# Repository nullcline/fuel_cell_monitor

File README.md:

# fuel_cell_monitor
[school] a sponsored capstone project to design a low-cost, scalable, voltage monitoring system that was capable of measuring a wide voltage range

here are some cool pics (i designed, manufactured, and tested the module).

you can read about the design in the included report [here](https://github.com/nullcline/fuel_cell_monitor/blob/main/design_report.pdf)

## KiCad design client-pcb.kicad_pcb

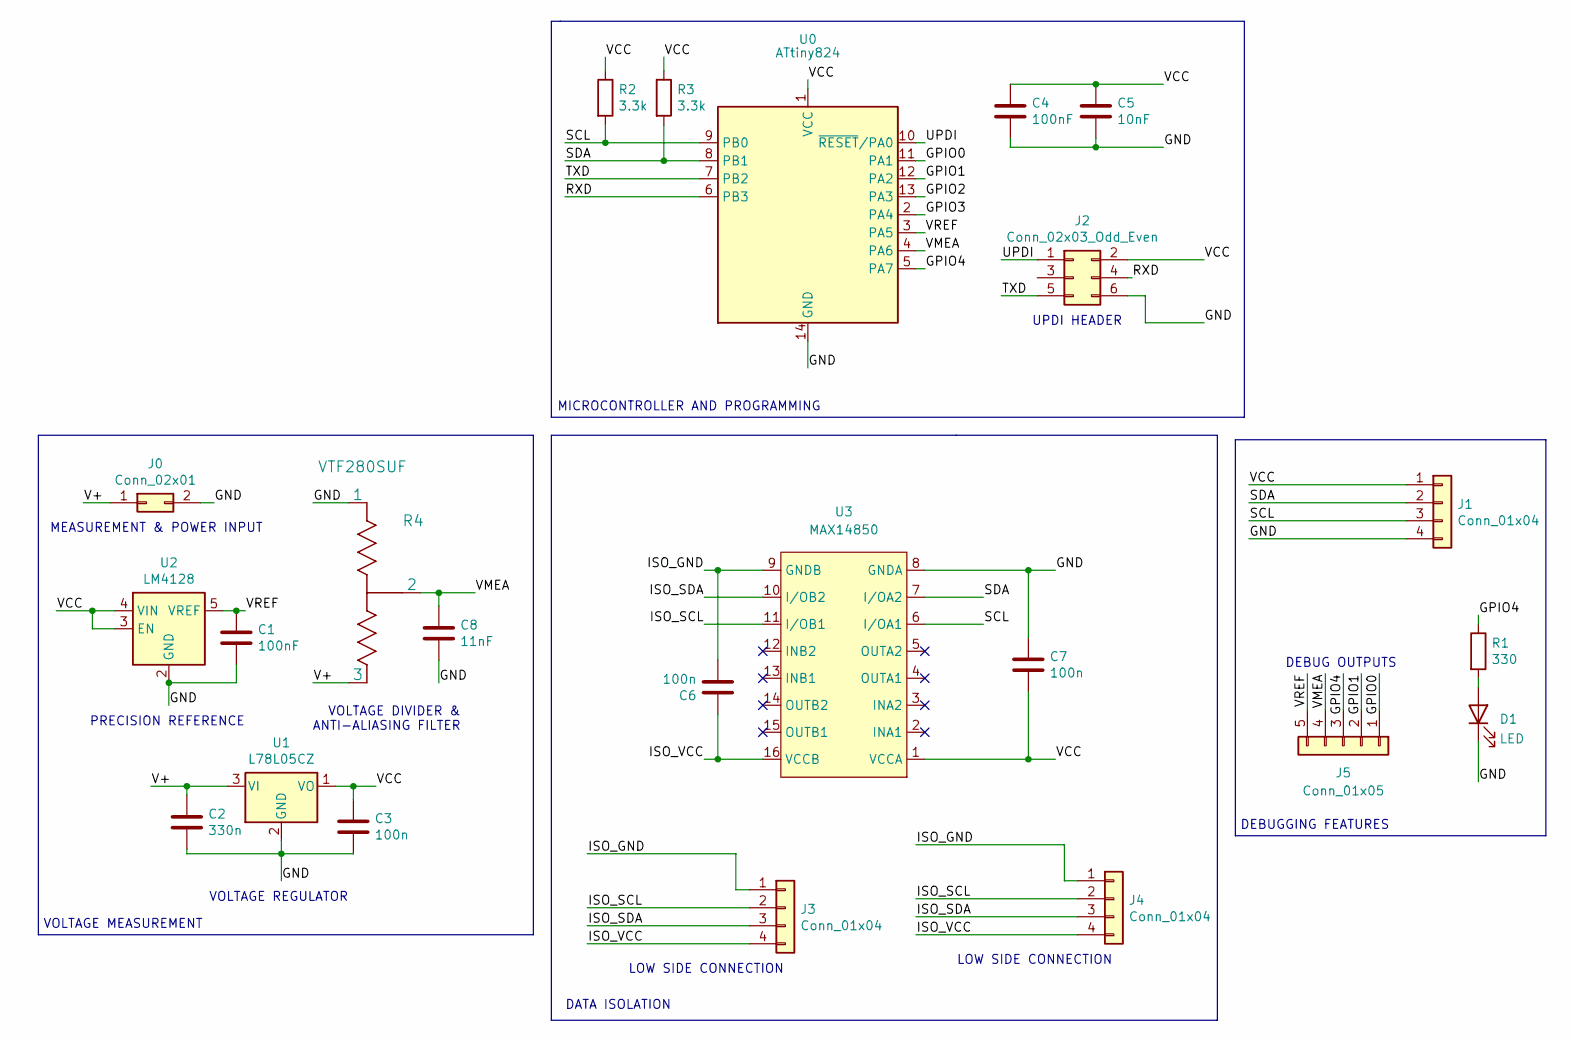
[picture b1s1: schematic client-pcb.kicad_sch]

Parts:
C1, C4: 100nF; C_1210_3225Metric_Pad1.33x2.70mm_HandSolder
C2: 330n; C_1210_3225Metric_Pad1.33x2.70mm_HandSolder
C3, C6, C7: 100n; C_1210_3225Metric_Pad1.33x2.70mm_HandSolder
C5: 10nF; C_1210_3225Metric_Pad1.33x2.70mm_HandSolder
C8: 11nF; C_1210_3225Metric_Pad1.33x2.70mm_HandSolder
D1: LED; LED_1210_3225Metric_Pad1.42x2.65mm_HandSolder
J0: Conn_02x01; TerminalBlock_Altech_AK300-2_P5.00mm
J1, J3, J4: Conn_01x04; PinHeader_1x04_P2.54mm_Vertical
J2: Conn_02x03_Odd_Even; PinHeader_2x03_P2.54mm_Vertical
J5: Conn_01x05; PinHeader_1x05_P2.54mm_Vertical
R1: 330; R_1210_3225Metric_Pad1.30x2.65mm_HandSolder
R2, R3: 3.3k; R_1210_3225Metric_Pad1.30x2.65mm_HandSolder
R4: VTF280SUF; PinSocket_1x03_P2.54mm_Vertical
U0: ATtiny824; SOIC-14_3.9x8.7mm_P1.27mm
U1: L78L05CZ; TO-92_Inline
U2: LM4128; SOT-23-5
U3: MAX14850; SOP-16_3.9x9.9mm_P1.27mm

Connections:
/GND: C1.2, C2.2, C3.2, C4.2, C5.2, C7.1, C8.2, D1.1 (K), J0.2, J1.4, J2.6, R4.1, U0.14 (GND), U1.2 (GND), U2.2 (GND), U3.8 (GNDA)
/GPIO0: J5.1, U0.11 (PA1)
/GPIO1: J5.2, U0.12 (PA2)
/GPIO2: U0.13 (PA3)
/GPIO3: U0.2 (PA4)
/GPIO4: J5.3, R1.1, U0.5 (PA7)
/ISO_GND: C6.2, J3.1, J4.1, U3.9 (GNDB)
/ISO_SCL: J3.2, J4.2, U3.11 (I/OB1)
/ISO_SDA: J3.3, J4.3, U3.10 (I/OB2)
/ISO_VCC: C6.1, J3.4, J4.4, U3.16 (VCCB)
/RXD: J2.4, U0.6 (PB3)
/SCL: J1.3, R2.2, U0.9 (PB0), U3.6 (I/OA1)
/SDA: J1.2, R3.2, U0.8 (PB1), U3.7 (I/OA2)
/TXD: J2.5, U0.7 (PB2)
/UPDI: J2.1, U0.10 (~RESET/PA0)
/V+: C2.1, J0.1, R4.3, U1.3 (VI)
/VCC: C3.1, C4.1, C5.1, C7.2, J1.1, J2.2, R2.1, R3.1, U0.1 (VCC), U1.1 (VO), U2.3 (EN), U2.4 (VIN), U3.1 (VCCA)
/VMEA: C8.1, J5.4, R4.2, U0.4 (PA6)
/VREF: C1.1, J5.5, U0.3 (PA5), U2.5 (VREF)
unnamed: D1.2 (A), R1.2

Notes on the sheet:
DEBUGGING FEATURES
LOW SIDE CONNECTION
UPDI HEADER
VOLTAGE REGULATOR
VOLTAGE DIVIDER & ANTI-ALIASING FILTER
DATA ISOLATION
MICROCONTROLLER AND PROGRAMMING
MEASUREMENT & POWER INPUT
PRECISION REFERENCE
DEBUG OUTPUTS
VOLTAGE MEASUREMENT

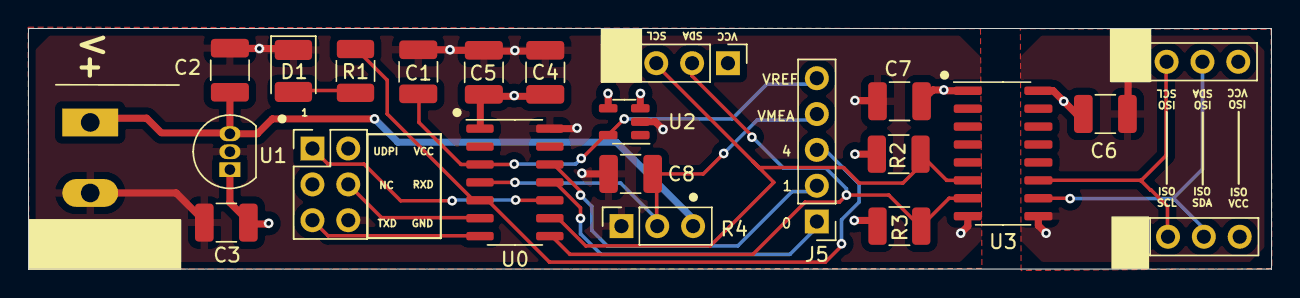
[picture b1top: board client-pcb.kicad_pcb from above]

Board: 4 copper layers, 88.1 x 17.1 mm, 23 parts (0 on the bottom side), 18 nets.

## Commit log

2023-07-04 pushing from drive
2023-09-28 added images and readme
